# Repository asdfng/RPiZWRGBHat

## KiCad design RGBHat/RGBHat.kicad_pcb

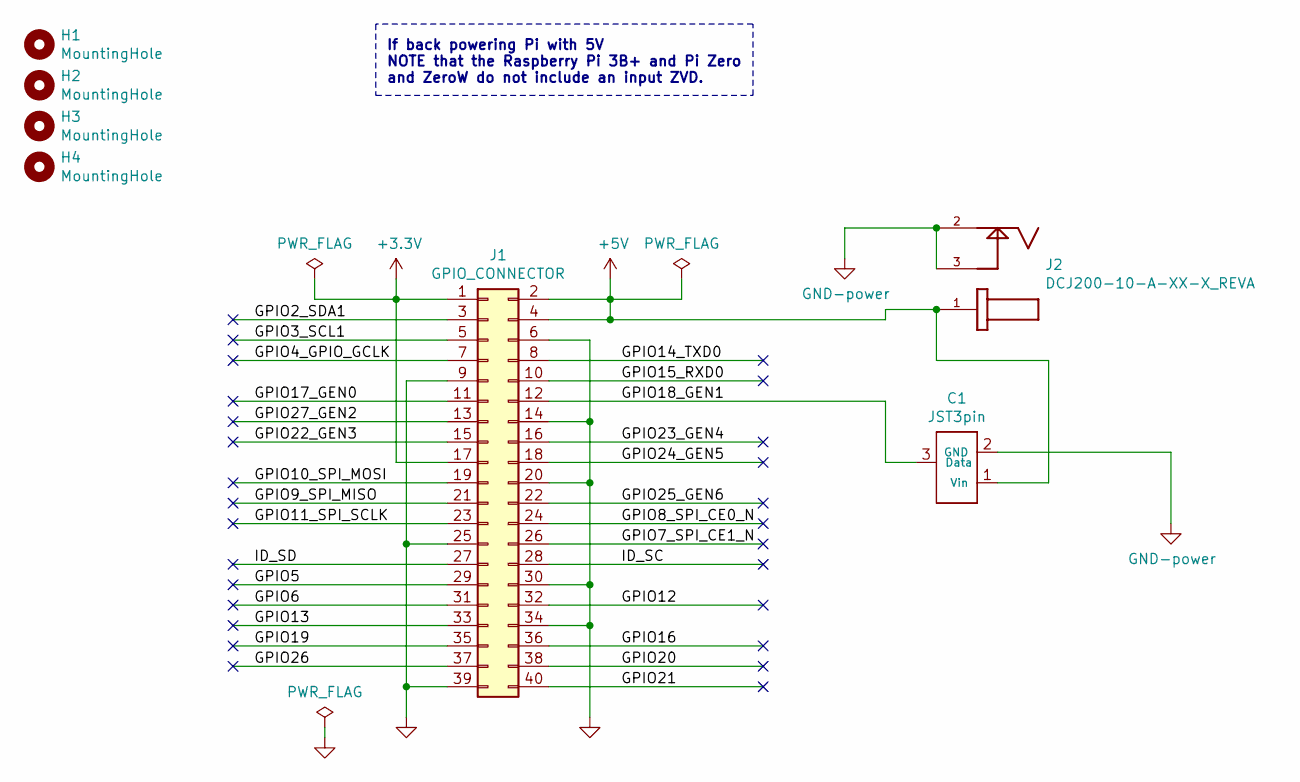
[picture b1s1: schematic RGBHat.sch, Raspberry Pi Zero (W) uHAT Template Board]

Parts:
C1: JST3pin; JST_Breakout
H1, H2, H3, H4: MountingHole; MountingHole_2.7mm_M2.5_uHAT_RPi
J1: GPIO_CONNECTOR; PinSocket_2x20_P2.54mm_Vertical_Centered_Anchor
J2: DCJ200-10-A-XX-X_REVA; GCT_DCJ200-10-A-XX-X_REVA

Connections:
+3V3: J1.1, J1.17
+5V: C1.1 (Vin), J1.2, J1.4, J2.1
/GPIO2_SDA1: J1.3
/GPIO3_SCL1: J1.5
/GPIO4_GPIO_GCLK: J1.7
/GPIO5: J1.29
/GPIO6: J1.31
/GPIO7_SPI_CE1_N: J1.26
/GPIO8_SPI_CE0_N: J1.24
/GPIO9_SPI_MISO: J1.21
/GPIO10_SPI_MOSI: J1.19
/GPIO11_SPI_SCLK: J1.23
/GPIO12: J1.32
/GPIO13: J1.33
/GPIO14_TXD0: J1.8
/GPIO15_RXD0: J1.10
/GPIO16: J1.36
/GPIO17_GEN0: J1.11
/GPIO18_GEN1: C1.3 (Data), J1.12
/GPIO19: J1.35
/GPIO20: J1.38
/GPIO21: J1.40
/GPIO22_GEN3: J1.15
/GPIO23_GEN4: J1.16
/GPIO24_GEN5: J1.18
/GPIO25_GEN6: J1.22
/GPIO26: J1.37
/GPIO27_GEN2: J1.13
/ID_SC: J1.28
/ID_SD: J1.27

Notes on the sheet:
If back powering Pi with 5V NOTE that the Raspberry Pi 3B+ and Pi Zero and ZeroW do not include an input ZVD.

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
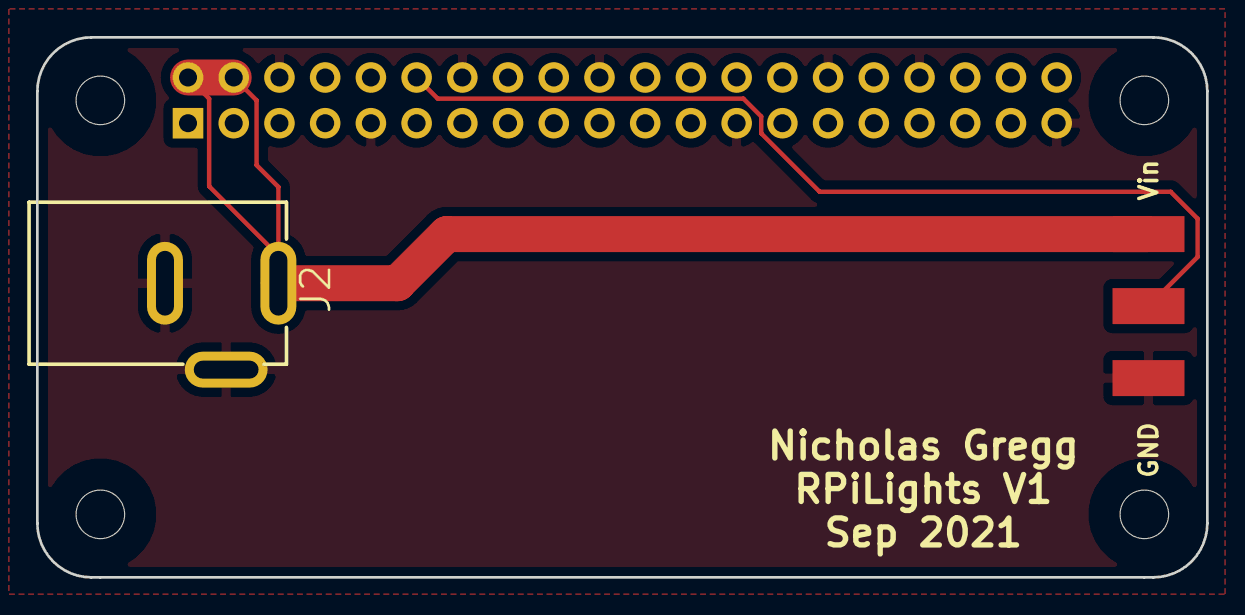
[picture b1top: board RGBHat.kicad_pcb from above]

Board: 2 copper layers, 65.0 x 30.0 mm, 7 parts (1 on the bottom side), 4 nets.

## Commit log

2021-09-06 Small Board for RGB strip
    Small board for RGB strip controller by RPi Zero W and Homebridge

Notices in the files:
RGBHat/RGBHat.kicad_pcb:
This PCB design is licensed under MIT Open Source License.
RGBHat/RGBHat.sch:
This Schematic is licensed under MIT Open Source License.
